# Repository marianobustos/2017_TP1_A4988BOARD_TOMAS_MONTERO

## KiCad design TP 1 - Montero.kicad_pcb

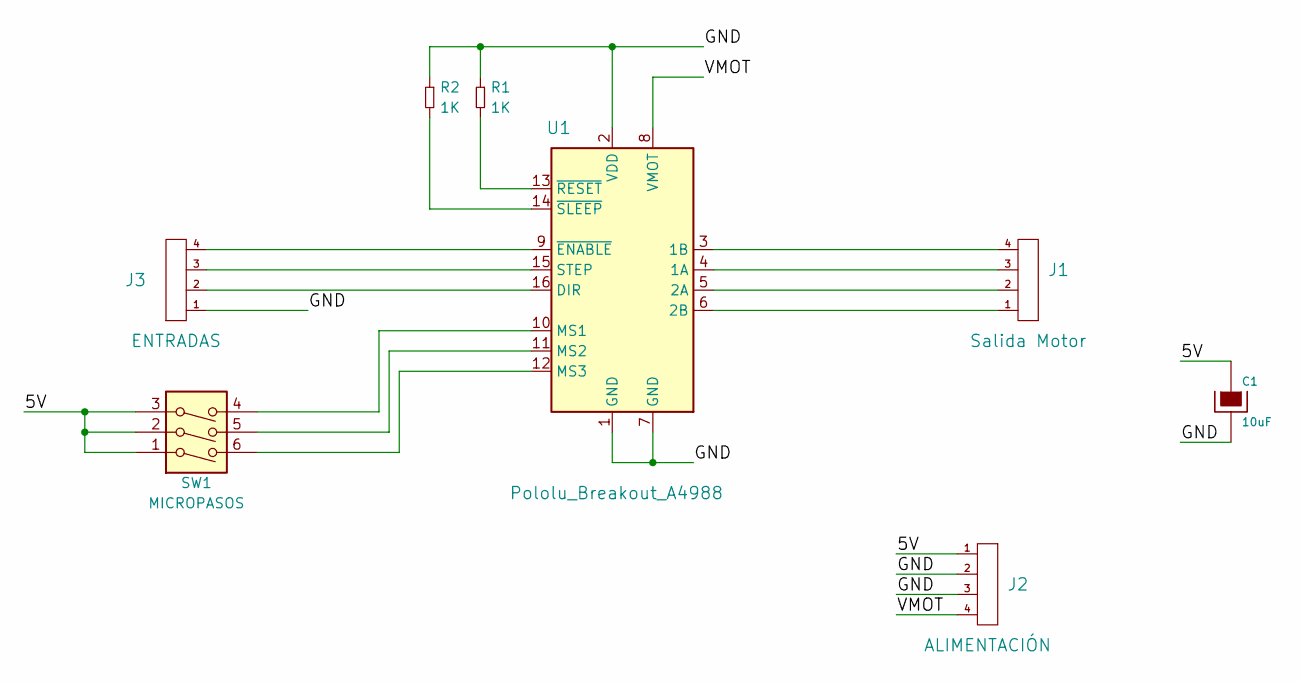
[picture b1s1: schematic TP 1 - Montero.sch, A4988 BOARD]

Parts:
C1: 10uF; CAP_0.1
J1: Salida Motor; HEADER-4H
J2: ALIMENTACIÓN; HEADER-4H
J3: ENTRADAS; HEADER-4H
R1, R2: 1K; R_1206
SW1: MICROPASOS; Dip_SW_3-300
U1: Pololu_Breakout_A4988; DRV8825

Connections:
/5V: C1.1, J2.1, SW1.1, SW1.2, SW1.3
/GND: C1.2, J2.2, J2.3, J3.1, R1.1, R2.1, U1.1 (GND), U1.2 (VDD), U1.7 (GND)
/VMOT: J2.4, U1.8 (VMOT)
unnamed: J1.1, U1.6 (2B)
unnamed: J1.2, U1.5 (2A)
unnamed: J1.3, U1.4 (1A)
unnamed: J1.4, U1.3 (1B)
unnamed: J3.2, U1.16 (DIR)
unnamed: J3.3, U1.15 (STEP)
unnamed: J3.4, U1.9 (~ENABLE)
unnamed: R1.2, U1.13 (~RESET)
unnamed: R2.2, U1.14 (~SLEEP)
unnamed: SW1.4, U1.10 (MS1)
unnamed: SW1.5, U1.11 (MS2)
unnamed: SW1.6, U1.12 (MS3)

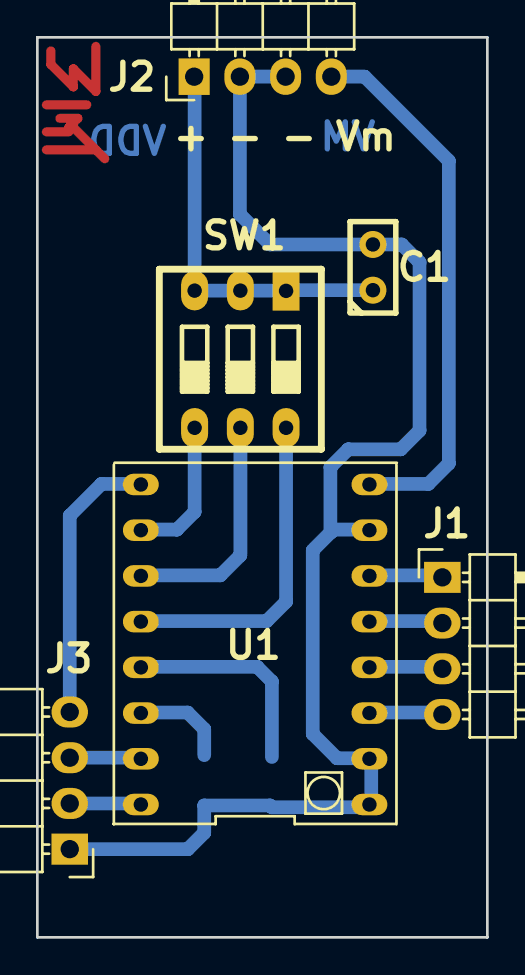
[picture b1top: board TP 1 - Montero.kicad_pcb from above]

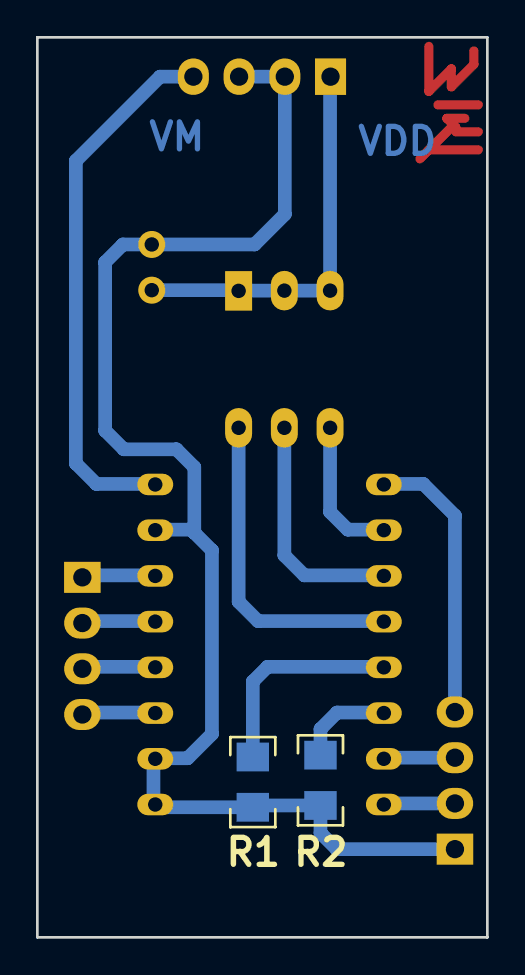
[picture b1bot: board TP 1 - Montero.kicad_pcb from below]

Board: 2 copper layers, 25.0 x 50.0 mm, 8 parts (2 on the bottom side), 15 nets.

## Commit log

2018-03-25 Documentación del proyecto
    Archivo de vista 3D, archivo para transferir el diseño a la placa de cobre y el esquemático en pdf para una visualización rápida.
